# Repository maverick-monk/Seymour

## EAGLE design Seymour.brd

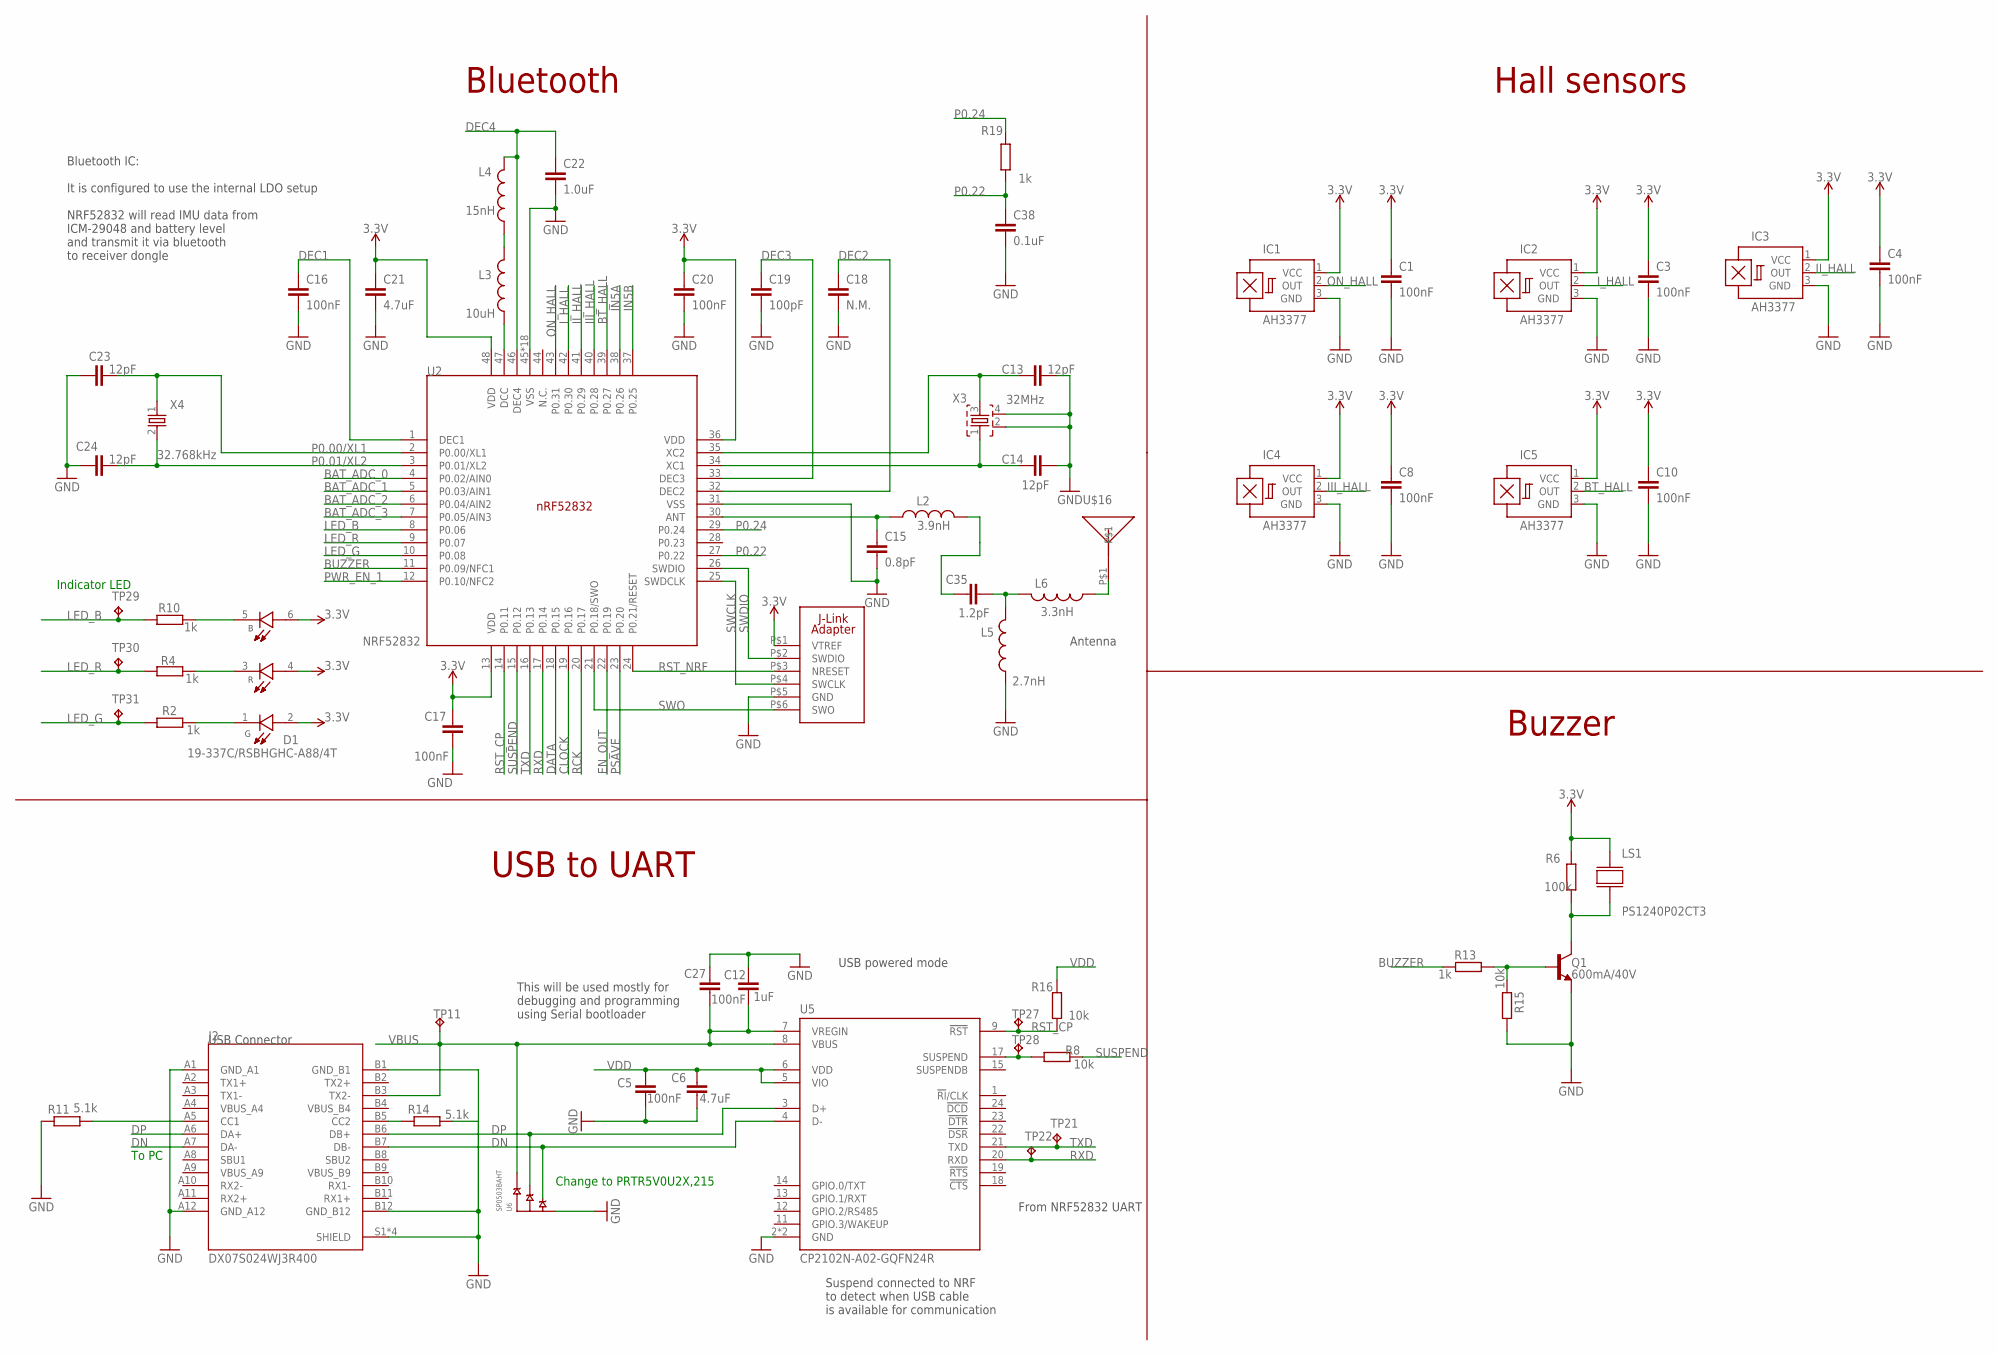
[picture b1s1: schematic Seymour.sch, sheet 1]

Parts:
C1, C3, C4, C5, C8, C10, C17, C20, C27: 100nF; C0402
C6, C21: 4.7uF; C0603
C12: 1uF; C0603
C13, C14, C23, C24: 12pF; C0402
C15: 0.8pF; C0402
C16: 100nF; C0603
C18: N.M.; C0603
C19: 100pF; C0402
C22: 1.0uF; C0603
C35: 1.2pF; RESC0402_N
C38: 0.1uF; C0402
D1: 19-337C/RSBHGHC-A88/4T; LED_19-337C/RSBHGHC-A88/4T
IC1, IC2, IC3, IC4, IC5: AH3377; SOT23-W
J2: DX07S024WJ3R400; JAE_DX07S024WJ3R400
L2: 3.9nH; RESC0402_N
L3: 10uH; RESC0603_N
L4: 15nH; RESC0402_N
L5: 2.7nH; RESC0402_N
L6: 3.3nH; RESC0402_N
LS1: PS1240P02CT3; XDCR_PS1240P02CT3
Q1: 600mA/40V; SOT23-3
R2, R4, R10, R13, R19: 1k; R0402
R6: 100k; R0402
R8, R15, R16: 10k; R0402
R11, R14: 5.1k; R0402
TP11, TP21, TP22, TP27, TP28, TP29, TP30, TP31: TPTP06R; TP06R
U2: NRF52832; QFN40P600X600X90-48_N
U5: CP2102N-A02-GQFN24R; QFN50P400X400X80-25N
U6: SP0503BAHT; SOT143
U$1: J-LINK_6-PIN_ADAPTER-1; J-LINK_6-PIN_ADAPTER_S
U$16: ANT_2450AT18B100E; 2450AT18B100E
X3: 32MHz; BT-XTAL_2016_N
X4: 32.768kHz; XTAL_3215_N

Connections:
3.3V: C1.1, C3.1, C4.1, C8.1, C10.1, C17.1, C20.1, C21.1, D1.2 (G_A), D1.4 (R_A), D1.6 (B_A), IC1.1 (VCC), IC2.1 (VCC), IC3.1 (VCC), IC4.1 (VCC), IC5.1 (VCC), LS1.2, R6.1, U2.13 (VDD), U2.36 (VDD), U2.48 (VDD), U$1.P$1 (VTREF); also elsewhere on the board
ANT1: C15.1, L2.1, U2.30 (ANT)
BAT_ADC_0: U2.4 (P0.02/AIN0); also elsewhere on the board
BAT_ADC_1: U2.5 (P0.03/AIN1); also elsewhere on the board
BAT_ADC_2: U2.6 (P0.04/AIN2); also elsewhere on the board
BAT_ADC_3: U2.7 (P0.05/AIN3); also elsewhere on the board
BT_HALL: IC5.2 (OUT), U2.39 (P0.27)
BUZZER: R13.1, U2.11 (P0.09/NFC1)
CLOCK: U2.19 (P0.16); also elsewhere on the board
DATA: U2.18 (P0.15); also elsewhere on the board
DEC1: C16.1, U2.1 (DEC1)
DEC2: C18.1, U2.32 (DEC2)
DEC3: C19.1, U2.33 (DEC3)
DEC4: C22.1, L4.2, U2.46 (DEC4)
DN: J2.A7 (DA-), J2.B7 (DB-), U5.4 (D-), U6.2 (A)
DP: J2.A6 (DA+), J2.B6 (DB+), U5.3 (D+), U6.3 (B)
EN_OUT: U2.22 (P0.19); also elsewhere on the board
GND: C1.2, C3.2, C4.2, C5.1, C6.2, C8.2, C10.2, C12.1, C13.2, C14.2, C15.2, C16.2, C17.2, C18.2, C19.2, C20.2, C21.2, C22.2, C23.1, C24.1, C27.2, C38.2, IC1.3 (GND), IC2.3 (GND), IC3.3 (GND), IC4.3 (GND), IC5.3 (GND), J2.A1 (GND_A1), J2.A12 (GND_A12), J2.B1 (GND_B1), J2.B12 (GND_B12), J2.S1 (SHIELD), J2.S2 (SHIELD), J2.S3 (SHIELD), J2.S4 (SHIELD), L5.1, Q1.2 (E), R11.1, R14.2, R15.2, U2.31 (VSS), U2.45 (VSS), U2.PAD (VSS), U2.PAD@VIA01 (VSS), U2.PAD@VIA02 (VSS), U2.PAD@VIA03 (VSS), U2.PAD@VIA04 (VSS), U2.PAD@VIA05 (VSS), U2.PAD@VIA06 (VSS), U2.PAD@VIA07 (VSS), U2.PAD@VIA08 (VSS), U2.PAD@VIA09 (VSS), U2.PAD@VIA10 (VSS), U2.PAD@VIA11 (VSS), U2.PAD@VIA12 (VSS), U2.PAD@VIA13 (VSS), U2.PAD@VIA14 (VSS), U2.PAD@VIA15 (VSS), U2.PAD@VIA16 (VSS), U5.2 (GND), U5.25 (GND), U6.1 (GND), U$1.P$5 (GND), X3.2, X3.4; also elsewhere on the board
III_HALL: IC4.2 (OUT), U2.40 (P0.28)
II_HALL: IC3.2 (OUT), U2.41 (P0.29)
IN5A: U2.38 (P0.26); also elsewhere on the board
IN5B: U2.37 (P0.25); also elsewhere on the board
I_HALL: IC2.2 (OUT), U2.42 (P0.30)
LED_B: R10.2, TP29.TP, U2.8 (P0.06)
LED_G: R2.2, TP31.TP, U2.10 (P0.08)
LED_R: R4.2, TP30.TP, U2.9 (P0.07); also elsewhere on the board
unnamed: C13.1, U2.35 (XC2), X3.3
unnamed: C35.2, L2.2
unnamed: R8.1, TP28.TP, U5.17 (SUSPEND)
unnamed: J2.A5 (CC1), R11.2
unnamed: J2.B5 (CC2), R14.1
unnamed: D1.3 (R_C), R4.1
unnamed: D1.5 (B_C), R10.1
unnamed: Q1.1 (B), R13.2, R15.1
unnamed: D1.1 (G_C), R2.1
unnamed: LS1.1, Q1.3 (C), R6.2
unnamed: L3.1, U2.47 (DCC)
unnamed: L3.2, L4.1
unnamed: C35.1, L5.2, L6.2
unnamed: L6.1, U$16.P$1
ON_HALL: IC1.2 (OUT), U2.43 (P0.31)
P0.00/XL1: C23.2, U2.2 (P0.00/XL1), X4.1
P0.01/XL2: C24.2, U2.3 (P0.01/XL2), X4.2
P0.22: C38.1, R19.1, U2.27 (P0.22)
P0.24: R19.2, U2.29 (P0.24)
PSAVE: U2.23 (P0.20); also elsewhere on the board
PWR_EN_1: U2.12 (P0.10/NFC2); also elsewhere on the board
RCK: U2.20 (P0.17); also elsewhere on the board
RST_CP: R16.2, TP27.TP, U2.14 (P0.11), U5.9 (!RST)
RST_NRF: U2.24 (P0.21/RESET), U$1.P$3 (NRESET)
RXD: TP22.TP, U2.17 (P0.14), U5.20 (RXD)
SUSPEND: R8.2, U2.15 (P0.12)
SWCLK: U2.25 (SWDCLK), U$1.P$4 (SWCLK)
SWDIO: U2.26 (SWDIO), U$1.P$2 (SWDIO)
SWO: U2.21 (P0.18/SWO), U$1.P$6 (SWO)
TXD: TP21.TP, U2.16 (P0.13), U5.21 (TXD)
VBUS: C12.2, C27.1, J2.B3 (TX2-), TP11.TP, U5.7 (VREGIN), U5.8 (VBUS), U6.4 (C); also elsewhere on the board
VDD: C5.2, C6.1, R16.1, U5.5 (VIO), U5.6 (VDD)
X2: C14.1, U2.34 (XC1), X3.1

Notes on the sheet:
Bluetooth
Indicator LED
Bluetooth IC: It is configured to use the internal LDO setup NRF52832 will read IMU data from ICM-29048 and battery level and transmit it via bluetooth to receiver dongle
From NRF52832 UART
To PC
USB to UART
USB Connector
Antenna
Suspend connected to NRF to detect when USB cable is available for communication
USB powered mode
This will be used mostly for debugging and programming using Serial bootloader
Change to PRTR5V0U2X,215‎
Hall sensors
Buzzer

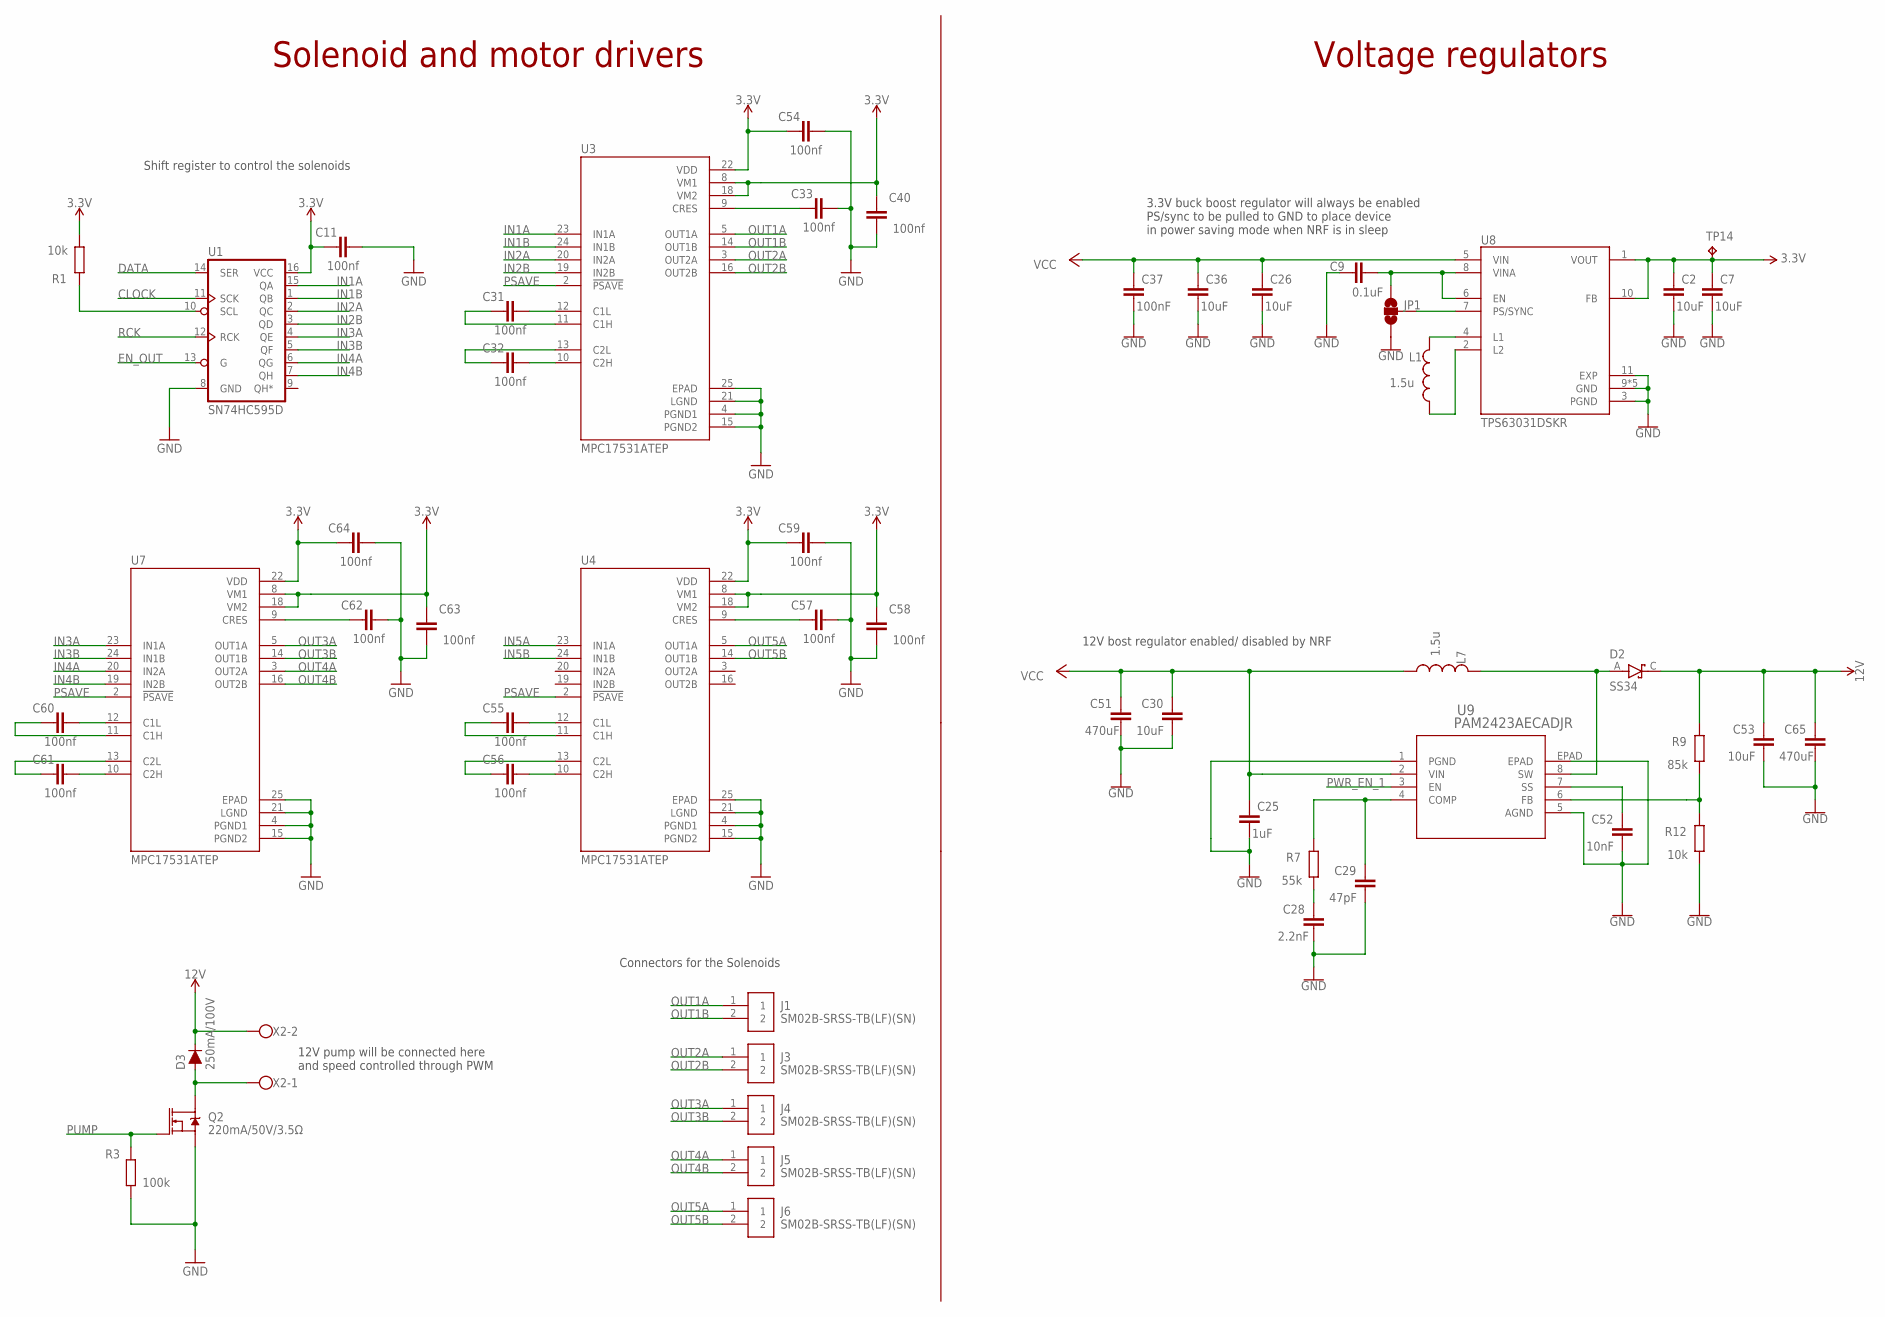
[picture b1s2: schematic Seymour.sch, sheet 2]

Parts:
C2, C7, C26, C30, C36, C53: 10uF; C0603
C9: 0.1uF; C0603
C11, C31, C32, C33, C40, C54, C55, C56, C57, C58, C59, C60, C61, C62, C63, C64: 100nf; RESC0402_N
C25: 1uF; C0603
C28: 2.2nF; C0603
C29: 47pF; C0603
C37: 100nF; C0603
C51, C65: 470uF; C0603
C52: 10nF; C0603
D2: SS34; DIOM7959X265N
D3: 250mA/100V; SOD-323
J1, J3, J4, J5, J6: SM02B-SRSS-TB(LF)(SN)
JP1: SPARKFUN-JUMPERS_JUMPER-SMT_NC; SPARKFUN-JUMPERS_SMT-JUMPER_TRACE_SILK
L1, L7: 1.5u; XFL4020
Q2: 220mA/50V/3.5Ω; SOT23-3
R1, R12: 10k; R0402
R3: 100k; R0402
R7: 55k; R0402
R9: 85k; R0402
TP14: TPTP06R; TP06R
U1: SN74HC595D; SO16
U3, U4, U7: MPC17531ATEP; QFN50P400X400X100-25N
U8: TPS63031DSKR; SON50P250X250X80-11N
U9: PAM2423AECADJR; SOP-8_PAM2423AECADJR_DIO
X2: W237-102

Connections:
3.3V: C2.1, C7.1, C11.2, C40.1, C54.2, C58.1, C59.2, C63.1, C64.2, R1.2, TP14.TP, U1.16 (VCC), U3.8 (VM1), U3.18 (VM2), U3.22 (VDD), U4.8 (VM1), U4.18 (VM2), U4.22 (VDD), U7.8 (VM1), U7.18 (VM2), U7.22 (VDD), U8.1 (VOUT), U8.10 (FB); also elsewhere on the board
12V: C53.1, C65.1, D2.C (K), D3.C, R9.2, X2.2
CLOCK: U1.11 (SCK); also elsewhere on the board
DATA: U1.14 (SER); also elsewhere on the board
EN_OUT: U1.13 (G); also elsewhere on the board
GND: C2.2, C7.2, C9.1, C11.1, C25.2, C26.2, C28.2, C29.2, C30.2, C33.1, C36.2, C37.2, C40.2, C51.2, C52.2, C53.2, C54.1, C57.1, C58.2, C59.1, C62.1, C63.2, C64.1, C65.2, JP1.1, Q2.2 (S), R3.2, R12.1, U1.8 (GND), U3.4 (PGND1), U3.15 (PGND2), U3.21 (LGND), U3.25 (EPAD), U4.4 (PGND1), U4.15 (PGND2), U4.21 (LGND), U4.25 (EPAD), U7.4 (PGND1), U7.15 (PGND2), U7.21 (LGND), U7.25 (EPAD), U8.3 (PGND), U8.9 (GND), U8.11 (EXP), U8.12 (GND), U8.13 (GND), U8.14 (GND), U8.15 (GND), U9.1 (PGND), U9.5 (AGND), U9.EPAD; also elsewhere on the board
IN1A: U1.15 (QA), U3.23 (IN1A)
IN1B: U1.1 (QB), U3.24 (IN1B)
IN2A: U1.2 (QC), U3.20 (IN2A)
IN2B: U1.3 (QD), U3.19 (IN2B)
IN3A: U1.4 (QE), U7.23 (IN1A)
IN3B: U1.5 (QF), U7.24 (IN1B)
IN4A: U1.6 (QG), U7.20 (IN2A)
IN4B: U1.7 (QH), U7.19 (IN2B)
IN5A: U4.23 (IN1A); also elsewhere on the board
IN5B: U4.24 (IN1B); also elsewhere on the board
unnamed: C9.2, JP1.3, U8.6 (EN), U8.8 (VINA)
unnamed: L1.P$2 (2), U8.4 (L1)
unnamed: R1.1, U1.10 (SCL)
unnamed: L1.P$1 (1), U8.2 (L2)
unnamed: D2.A, L7.P$2 (2), U9.8 (SW)
unnamed: JP1.2, U8.7 (PS/SYNC)
unnamed: C29.1, R7.2, U9.4 (COMP)
unnamed: C28.1, R7.1
unnamed: C52.1, U9.7 (SS)
unnamed: R9.1, R12.2, U9.6 (FB)
unnamed: C32.1, U3.10 (C2H)
unnamed: C32.2, U3.13 (C2L)
unnamed: C31.2, U3.11 (C1H)
unnamed: C31.1, U3.12 (C1L)
unnamed: C33.2, U3.9 (CRES)
unnamed: D3.A, Q2.3 (D), X2.1
unnamed: C56.1, U4.10 (C2H)
unnamed: C56.2, U4.13 (C2L)
unnamed: C55.2, U4.11 (C1H)
unnamed: C55.1, U4.12 (C1L)
unnamed: C57.2, U4.9 (CRES)
unnamed: C61.1, U7.10 (C2H)
unnamed: C61.2, U7.13 (C2L)
unnamed: C60.2, U7.11 (C1H)
unnamed: C60.1, U7.12 (C1L)
unnamed: C62.2, U7.9 (CRES)
OUT1A: J1.1, U3.5 (OUT1A)
OUT1B: J1.2, U3.14 (OUT1B)
OUT2A: J3.1, U3.3 (OUT2A)
OUT2B: J3.2, U3.16 (OUT2B)
OUT3A: J4.1, U7.5 (OUT1A)
OUT3B: J4.2, U7.14 (OUT1B)
OUT4A: J5.1, U7.3 (OUT2A)
OUT4B: J5.2, U7.16 (OUT2B)
OUT5A: J6.1, U4.5 (OUT1A)
OUT5B: J6.2, U4.14 (OUT1B)
PSAVE: U3.2 (!PSAVE), U4.2 (!PSAVE), U7.2 (!PSAVE); also elsewhere on the board
PUMP: Q2.1 (G), R3.1
PWR_EN_1: U9.3 (EN); also elsewhere on the board
RCK: U1.12 (RCK); also elsewhere on the board
VCC: C25.1, C26.1, C30.1, C36.1, C37.1, C51.1, L7.P$1 (1), U8.5 (VIN), U9.2 (VIN); also elsewhere on the board

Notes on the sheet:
Voltage regulators
Solenoid and motor drivers
12V pump will be connected here and speed controlled through PWM
Connectors for the Solenoids
Shift register to control the solenoids
3.3V buck boost regulator will always be enabled PS/sync to be pulled to GND to place device in power saving mode when NRF is in sleep
12V bost regulator enabled/ disabled by NRF

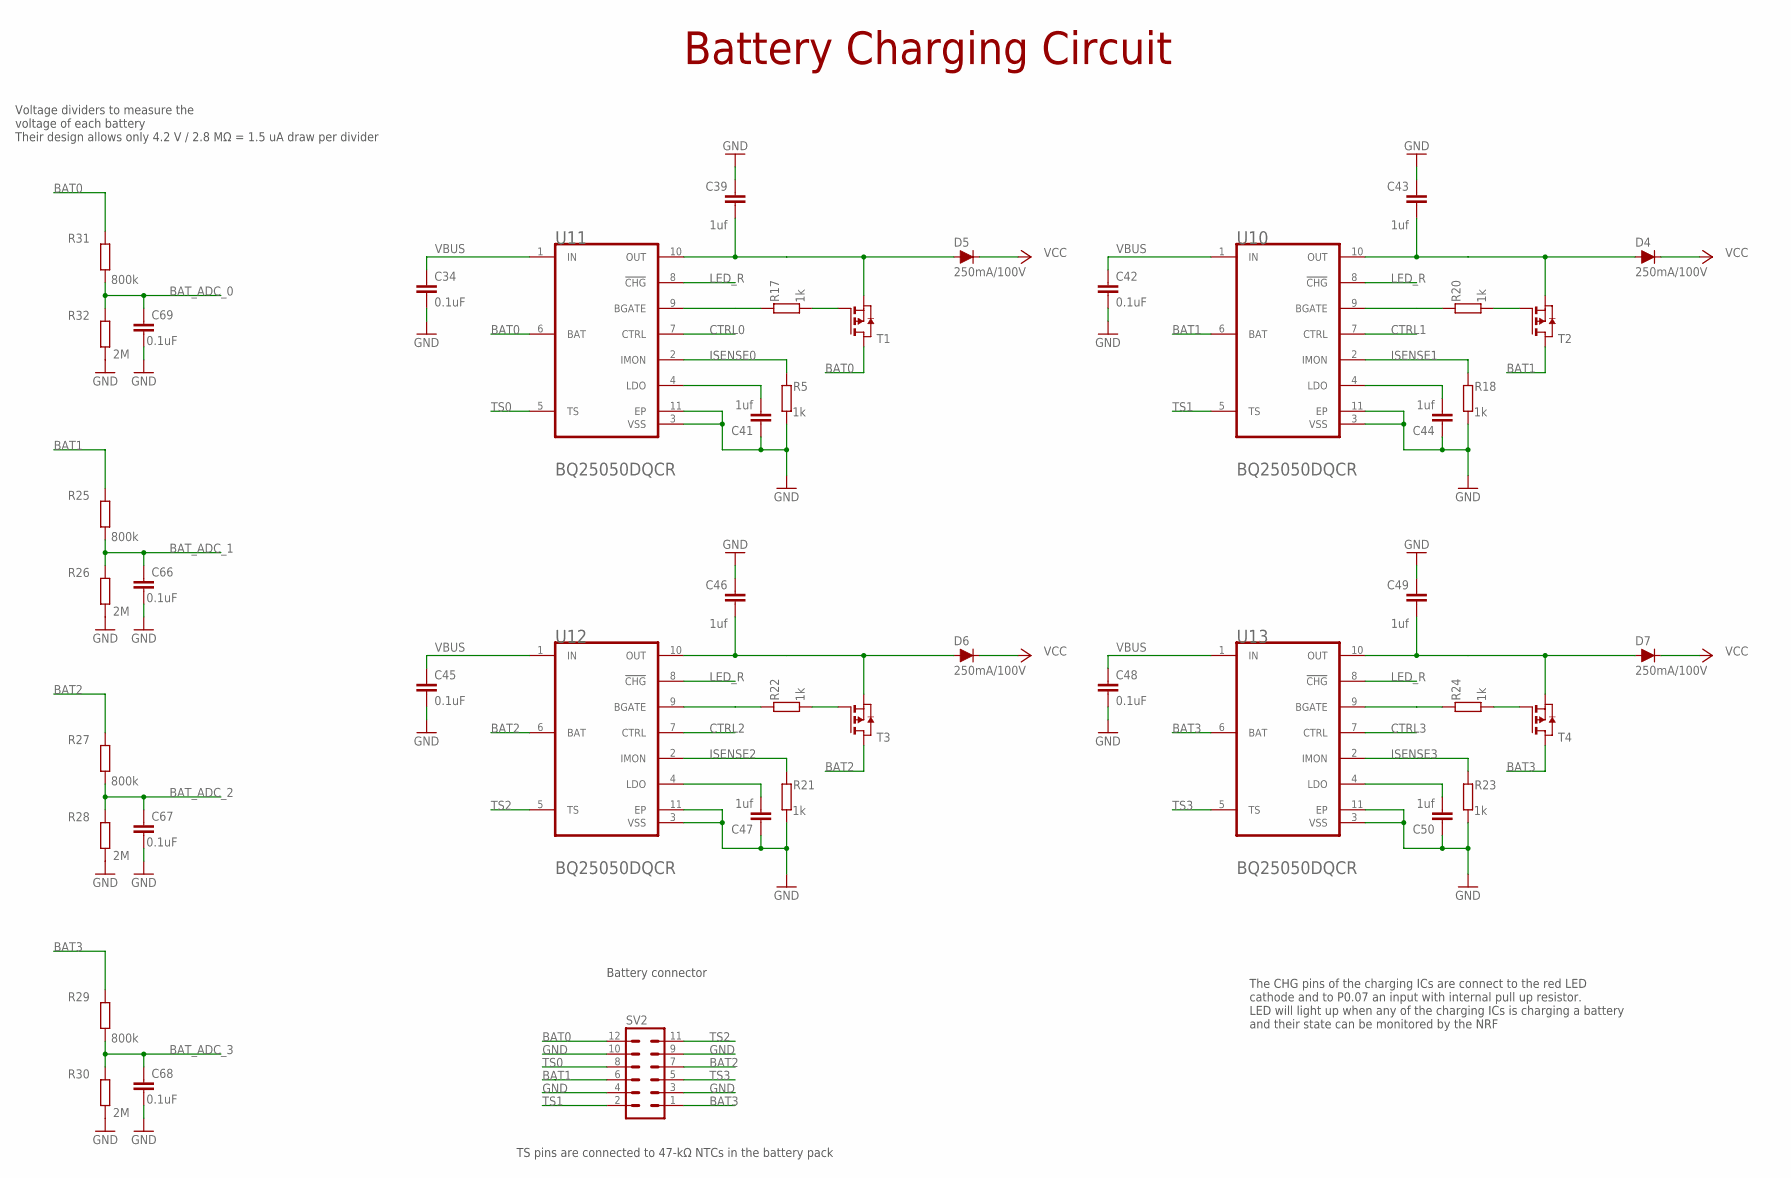
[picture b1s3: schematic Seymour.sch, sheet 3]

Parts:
C34, C42, C45, C48, C66, C67, C68, C69: 0.1uF; C0402
C39, C41, C43, C44, C46, C47, C49, C50: 1uf; C0402
D4, D5, D6, D7: 250mA/100V; SOD-323
R5, R17, R18, R20, R21, R22, R23, R24: 1k; R0402
R25, R27, R29, R31: 800k; R0402
R26, R28, R30, R32: 2M; R0402
SV2: MA06-2
T1, T2, T3, T4: PMOSSOT23; SOT-23
U10, U11, U12, U13: TEXAS_INSTRUMENTS_BQ25050DQCRTEXAS_INSTRUMENTS_BQ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; TEXAS_INSTRUMENTS_BQ25050DQCR_0

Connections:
BAT0: R31.2, SV2.12, T1.1 (D), U11.6 (BAT)
BAT1: R25.2, SV2.6, T2.1 (D), U10.6 (BAT)
BAT2: R27.2, SV2.7, T3.1 (D), U12.6 (BAT)
BAT3: R29.2, SV2.1, T4.1 (D), U13.6 (BAT)
BAT_ADC_0: C69.1, R31.1, R32.2; also elsewhere on the board
BAT_ADC_1: C66.1, R25.1, R26.2; also elsewhere on the board
BAT_ADC_2: C67.1, R27.1, R28.2; also elsewhere on the board
BAT_ADC_3: C68.1, R29.1, R30.2; also elsewhere on the board
CTRL0: U11.7 (CTRL)
CTRL1: U10.7 (CTRL)
CTRL2: U12.7 (CTRL)
CTRL3: U13.7 (CTRL)
GND: C34.2, C39.1, C41.1, C42.2, C43.1, C44.1, C45.2, C46.1, C47.1, C48.2, C49.1, C50.1, C66.2, C67.2, C68.2, C69.2, R5.1, R18.1, R21.1, R23.1, R26.1, R28.1, R30.1, R32.1, SV2.3, SV2.4, SV2.9, SV2.10, U10.3 (VSS), U10.11 (EP), U11.3 (VSS), U11.11 (EP), U12.3 (VSS), U12.11 (EP), U13.3 (VSS), U13.11 (EP); also elsewhere on the board
ISENSE0: R5.2, U11.2 (IMON)
ISENSE1: R18.2, U10.2 (IMON)
ISENSE2: R21.2, U12.2 (IMON)
ISENSE3: R23.2, U13.2 (IMON)
LED_R: U10.8 (!CHG!), U11.8 (!CHG!), U12.8 (!CHG!), U13.8 (!CHG!); also elsewhere on the board
unnamed: R17.1, T1.3 (G)
unnamed: R17.2, U11.9 (BGATE)
unnamed: C39.2, D5.A, T1.2 (S), U11.10 (OUT)
unnamed: C44.2, U10.4 (LDO)
unnamed: C41.2, U11.4 (LDO)
unnamed: C43.2, D4.A, T2.2 (S), U10.10 (OUT)
unnamed: R20.2, U10.9 (BGATE)
unnamed: R20.1, T2.3 (G)
unnamed: C47.2, U12.4 (LDO)
unnamed: C46.2, D6.A, T3.2 (S), U12.10 (OUT)
unnamed: R22.2, U12.9 (BGATE)
unnamed: R22.1, T3.3 (G)
unnamed: C50.2, U13.4 (LDO)
unnamed: C49.2, D7.A, T4.2 (S), U13.10 (OUT)
unnamed: R24.2, U13.9 (BGATE)
unnamed: R24.1, T4.3 (G)
TS0: SV2.8, U11.5 (TS)
TS1: SV2.2, U10.5 (TS)
TS2: SV2.11, U12.5 (TS)
TS3: SV2.5, U13.5 (TS)
VBUS: C34.1, C42.1, C45.1, C48.1, U10.1 (IN), U11.1 (IN), U12.1 (IN), U13.1 (IN); also elsewhere on the board
VCC: D4.C, D5.C, D6.C, D7.C; also elsewhere on the board

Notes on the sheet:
Battery Charging Circuit
The CHG pins of the charging ICs are connect to the red LED cathode and to P0.07 an input with internal pull up resistor. LED will light up when any of the charging ICs is charging a battery and their state can be monitored by the NRF
TS pins are connected to 47-kΩ NTCs in the battery pack
Battery connector
Voltage dividers to measure the voltage of each battery Their design allows only 4.2 V / 2.8 MΩ = 1.5 uA draw per divider

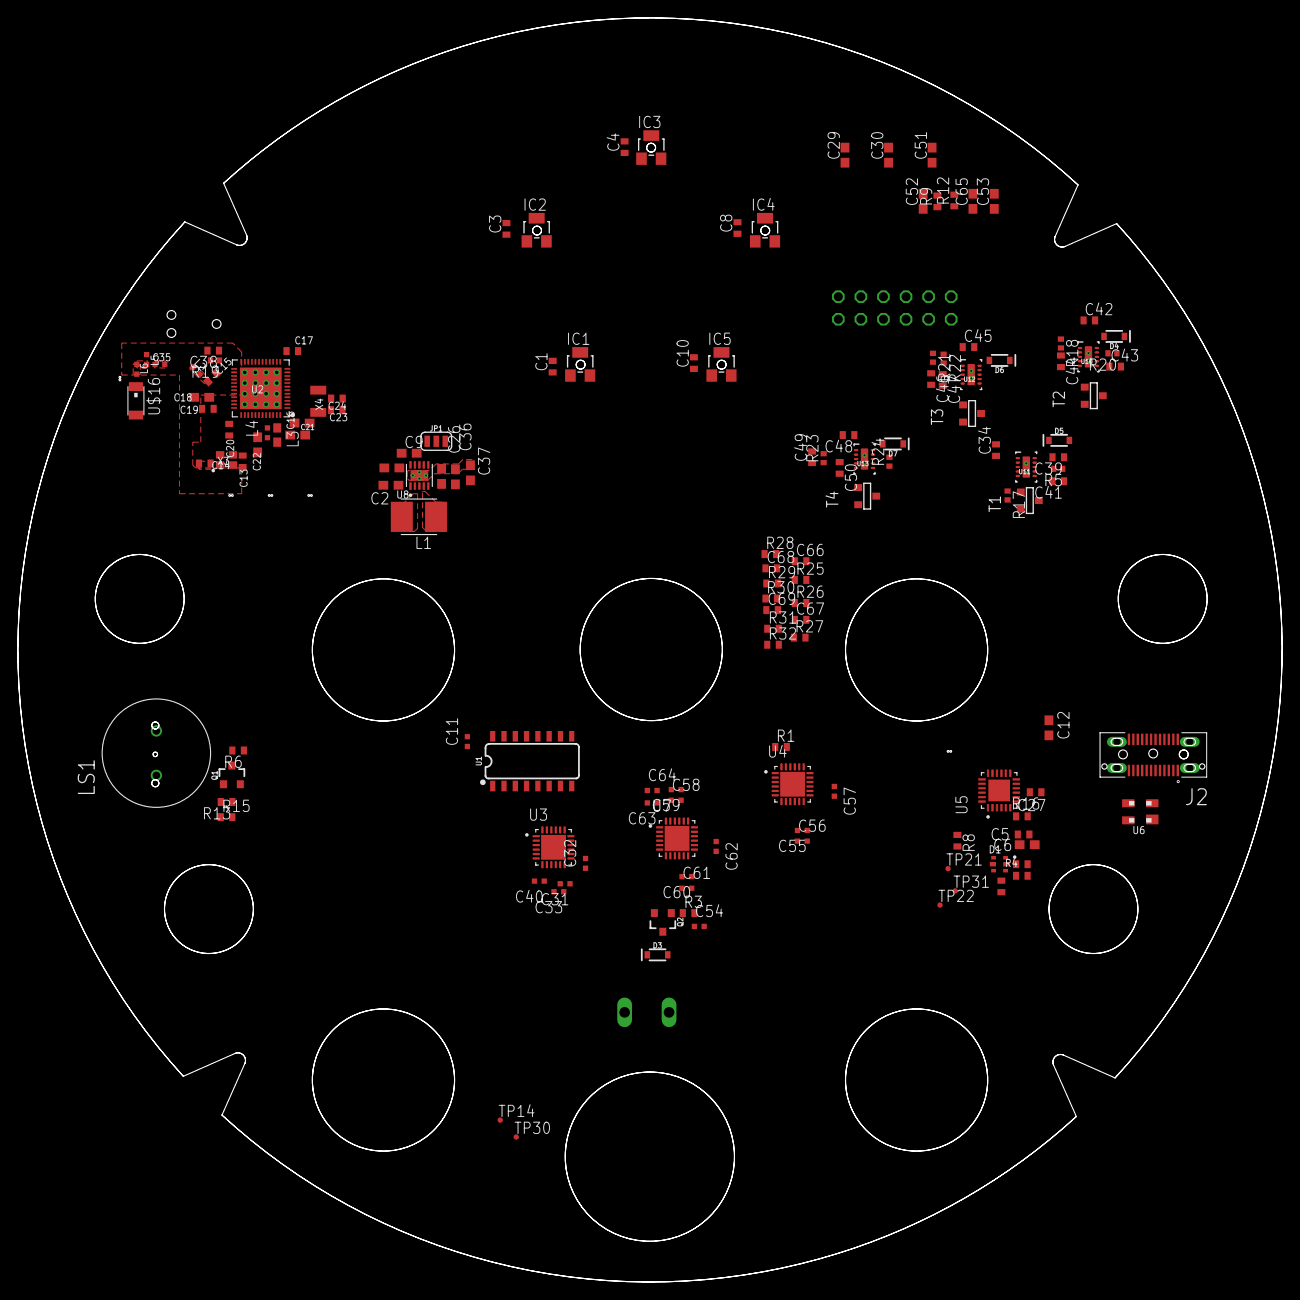
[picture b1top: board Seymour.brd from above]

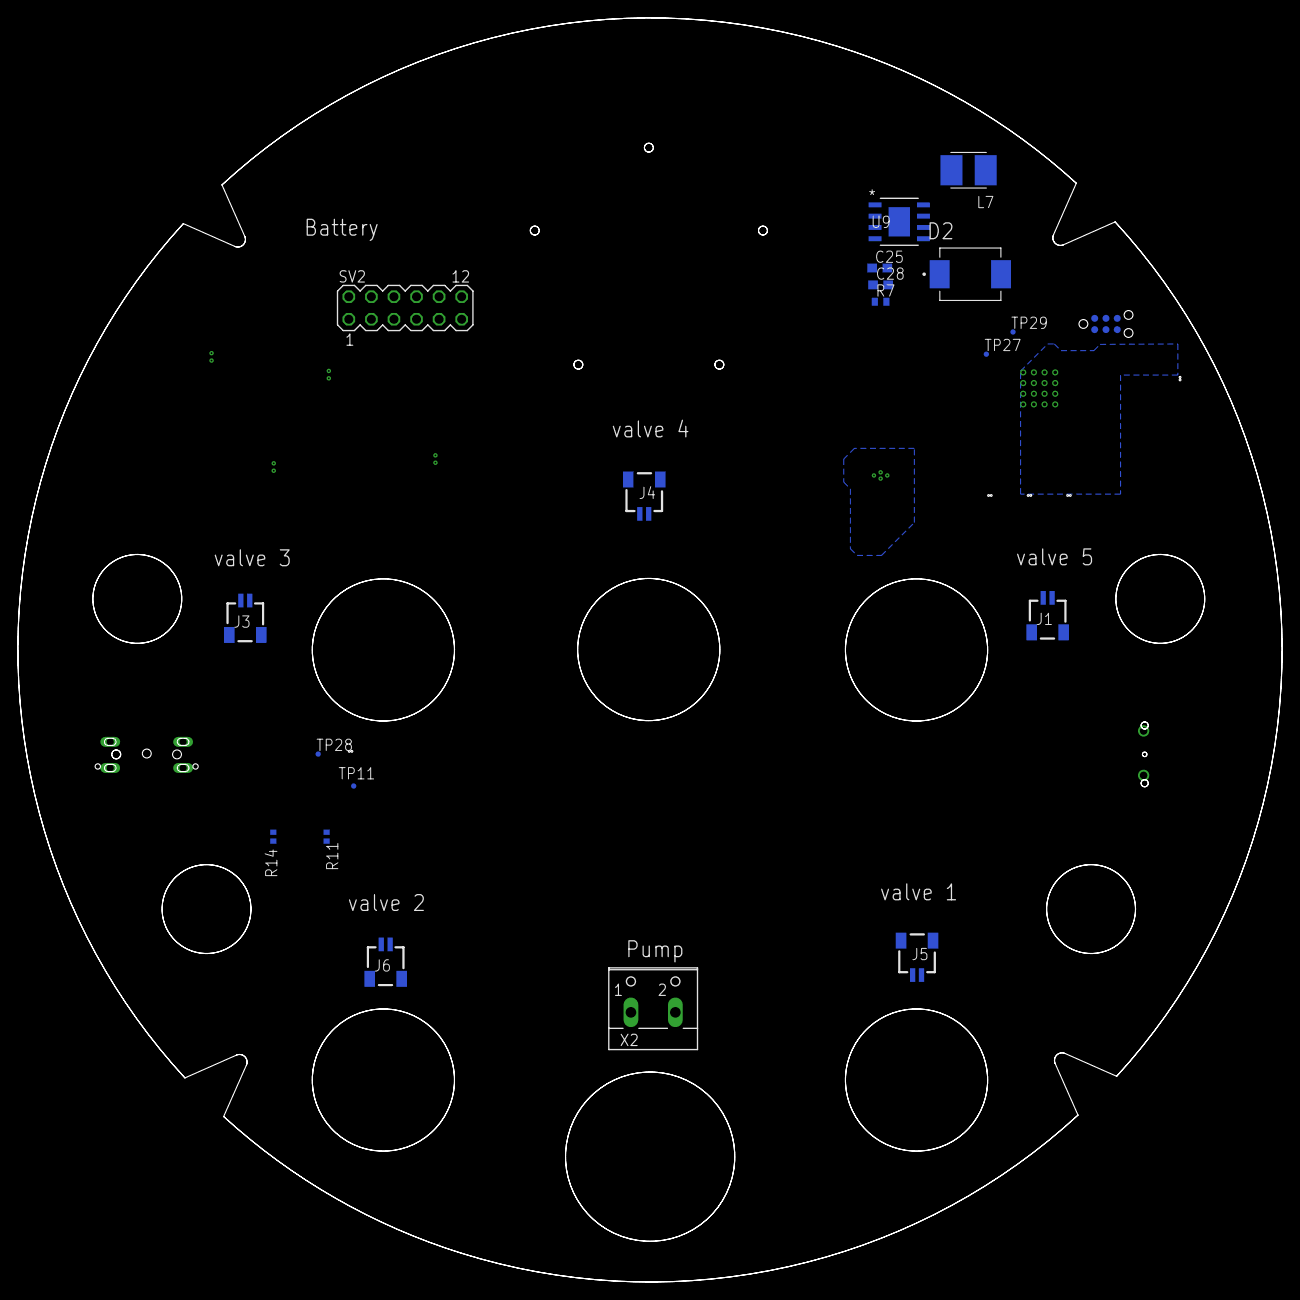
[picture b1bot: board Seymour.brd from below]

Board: 4 copper layers, 142.3 x 142.3 mm, 162 parts (20 on the bottom side), 134 nets.

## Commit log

2021-09-01 add project

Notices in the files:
parts and their libraries:
SparkFun-DiscreteSemi: Licensing: Creative Commons ShareAlike 4.0 International - https://creativecommons.org/licenses/by-sa/4.0
COPYRIGHT: Copyright (C) 2021 Ultra Librarian. All rights reserved.
